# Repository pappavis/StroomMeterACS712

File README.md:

Measure AC power usage using ESP8266 and ACS712

Werk-in-uitvoering!!!

# Waarom?
De bedoeling is om een 230V AC middels software te kunnen aan/uitzetten.  In principe kunt je dit gebruiken waar je AC stroom willen aan/uitzetten en meten. Het functioneert in principe dezelfde als een Sonoff POW switch.

# Hoe werkt het
Wanneer IO-pin HIGH op de ESP32 gaat de voeding aan, aangestuurd door Octoprint, vlak voor starten met printen.

# KiCAD schema

# Benodigheden
De volgende heb je nodig;

|Aantal|Item|Kosten|Optioneel|Data / info|
|------|----|------|---------|--|
|1x|<a href="https://nl.aliexpress.com/item/1005004344359250.html?spm=a2g0o.cart.0.0.6ca561d7aq0PVO&mp=1&gatewayAdapt=glo2nld" alt="MCU verplicht">ESP32 S2 Mini</a> met Bluetooth &amp; WiFi|€2,28|N|<a href="https://www.wemos.cc/en/latest/s2/s2_mini.html">datasheet</a>|
|1x|<a href="https://nl.aliexpress.com/item/32949264545.html?spm=a2g0o.productlist.main.1.1964577aTEmXD6&algo_pvid=6153c03f-b4b4-4653-a854-14e6c40e5aa0&aem_p4p_detail=202301040356468264624950022100000543353&algo_exp_id=6153c03f-b4b4-4653-a854-14e6c40e5aa0-0&pdp_ext_f=%7B%22sku_id%22%3A%2266268030503%22%7D&pdp_npi=2%40dis%21EUR%211.11%211.11%21%21%21%21%21%402145288516728334064801617d0767%2166268030503%21sea&curPageLogUid=MFJIrYuofizE&ad_pvid=202301040356468264624950022100000543353_1&ad_pvid=202301040356468264624950022100000543353_1" alt="AC stroom meten tot 20A">ACS712-05</a> breakout board|€1,11|N|<a href="https://octopart.com/datasheet/acs712elctr-05b-t-allegro+microsystems-38944601">datasheet</a>|J|
|1x|<a href="https://nl.aliexpress.com/item/32808620818.html?spm=a2g0o.order_list.order_list_main.5.2b0a79d2QUDt5m&gatewayAdapt=glo2nld">SRD-03VDC-SL-C 10A 250V</a> relay|€2,44|N|<a href="http://www.datasheetcafe.com/srd-05vdc-sl-c-datasheet-pdf/" alt="verplicht. aan uit schakelaar">datasheet</a>|
|1x|I2C <a href="https://nl.aliexpress.com/item/32672327708.html?spm=a2g0o.cart.0.0.5e6f61d7sThdsn&mp=1&gatewayAdapt=glo2nld" target="_blank">Oled 128X32 scherm</a>|€1,38|J|datasheet|
|1x|<a href="https://nl.aliexpress.com/item/1005003568092031.html?spm=a2g0o.productlist.main.7.30e378e19RwleU&algo_pvid=45aa2b55-53f0-4cf6-be4c-6e9c11d61f6f&aem_p4p_detail=202301040503385945494397516960000675494&algo_exp_id=45aa2b55-53f0-4cf6-be4c-6e9c11d61f6f-3&pdp_ext_f=%7B%22sku_id%22%3A%2212000030654022470%22%7D&pdp_npi=2%40dis%21EUR%215.04%213.93%21%21%21%21%21%402145265416728374183238677d0782%2112000030654022470%21sea&curPageLogUid=Hf4C5MspqKPZ&ad_pvid=202301040503385945494397516960000675494_4&ad_pvid=202301040503385945494397516960000675494_4">SPDT</a> tuimelschakelaar|€0,10|N|<a href="https://www.electronicshub.org/switches/" alt="hulp artikel">info</a>|
|1x|I2C <a href="https://nl.aliexpress.com/item/1005001682363363.html?spm=a2g0o.productlist.main.1.59bf3ddaYob59r&algo_pvid=b5a2e4fa-2b1d-4794-aa8b-f1d2eecffdef&aem_p4p_detail=202301040508292990992845371040000686338&algo_exp_id=b5a2e4fa-2b1d-4794-aa8b-f1d2eecffdef-0&pdp_ext_f=%7B%22sku_id%22%3A%2212000017115738926%22%7D&pdp_npi=2%40dis%21EUR%211.97%211.97%21%21%21%21%21%402145265416728377092613039d0782%2112000017115738926%21sea&curPageLogUid=OZkt1SVUV4Va&ad_pvid=202301040508292990992845371040000686338_1&ad_pvid=202301040508292990992845371040000686338_1">PCF8574P</a> 8-bit expander|€0,20|N|<a href="https://github.com/mcauser/micropython-pcf8574">info</a>|
|2|Screw <a href="https://nl.aliexpress.com/w/wholesale-screw-terminals.html?catId=0&initiative_id=AS_20230210044355&SearchText=screw+terminals&spm=a2g0o.cart.1000002.0" target="_blank">terminals</a>|€0,10|-|-|

Je kunt van Aliexpress bestellen die in één pakketje worden opgestuurd.

# Papier concept versie
TODO: onderstaand schema uitleggen.<br>
<br>
Credits: Max50

# Geïnspireerd door
heb de kunstje beetje geleend van;
 * <a href="https://www.youtube.com/watch?v=dQNBeAZpRmk" target="_blank">Deze</a> videoclip.
 * OctoPrint <a href="https://plugins.octoprint.org/plugins/psucontrol/" target="_blank">psucontrol</a> uitbreiding.

# Algemeen foto's
ACS712 breakout board &amp; <a href="https://octopart.com/datasheet/acs712elctr-05b-t-allegro+microsystems-38944601" target="_blank">datasheet</a>:<br>
</img>
<br>

Tip: PCB gcode voor jouw CNC machine kunt je genereren voor met <a href="http://flatcam.org" target="_blank">Flatcam.org</a>

Credit: <a href="https://www.youtube.com/@easylab4kids246" target="_blank">#easylab4kids</a>

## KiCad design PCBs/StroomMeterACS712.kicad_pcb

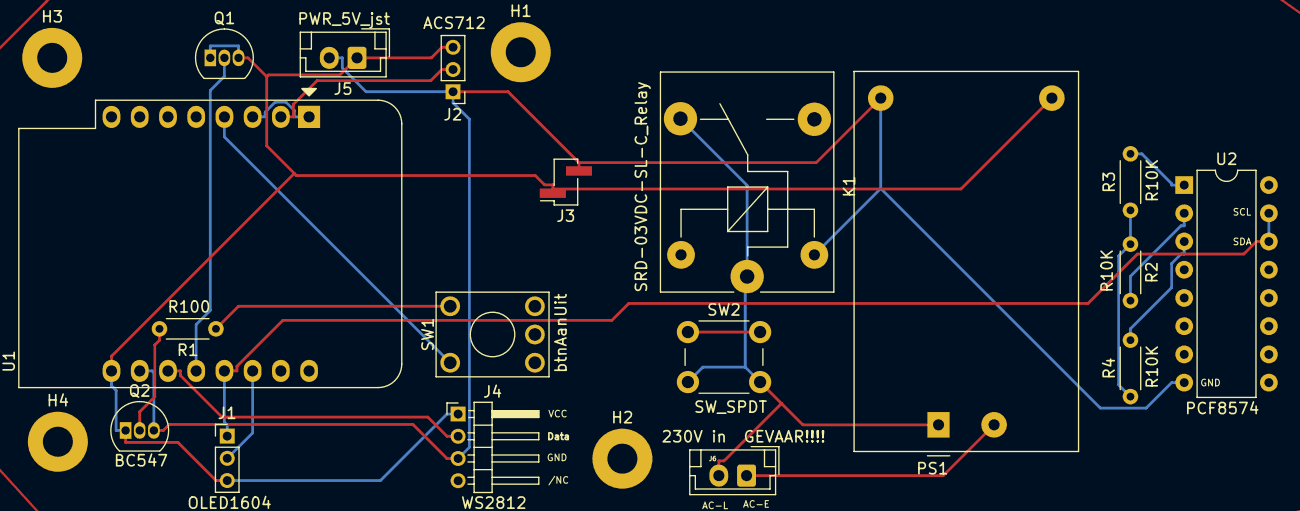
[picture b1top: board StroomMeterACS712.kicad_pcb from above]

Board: 2 copper layers, 22 parts (0 on the bottom side), 17 nets.

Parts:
H1, H2, H3, H4: Gaatje; MountingHole_2.7mm_M2.5_Pad
J1: OLED1604; PinHeader_1x03_P2.00mm_Vertical
J2: ACS712; PinHeader_1x03_P2.00mm_Vertical
J3: PWR_5V_pin; PinHeader_1x02_P2.00mm_Vertical_SMD_Pin1Right
J4: WS2812; PinHeader_1x04_P2.00mm_Horizontal
J5: PWR_5V_jst; JST_EH_B2B-EH-A_1x02_P2.50mm_Vertical
J6: 230V_in; JST_EH_B2B-EH-A_1x02_P2.50mm_Vertical
K1: SRD-03VDC-SL-C_Relay; Relay_SPDT_SANYOU_SRD_Series_Form_C
PS1: HLK-PM01_220V; Converter_ACDC_HiLink_HLK-PMxx
Q1, Q2: BC547; TO-92_Inline
R1: R100; R_Axial_DIN0204_L3.6mm_D1.6mm_P5.08mm_Horizontal
R2, R3, R4: R10K; R_Axial_DIN0204_L3.6mm_D1.6mm_P5.08mm_Horizontal
SW1: btnAanUit; KSA_Tactile_SPST
SW2: SW_SPDT; SW_PUSH_6mm
U1: WeMos_D1_mini; WEMOS_D1_mini_light
U2: PCF8574A; DIP-16_W7.62mm

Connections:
+5V: R2.1, R3.1, R4.1
ACS_AanUit: Q1.2 (B), U1.12 (D3), U2.4 (P0)
ACS_DATA: J2.2, U1.2 (A0)
AC/L: J6.2, K1.1, K1.4, PS1.1 (AC/L), SW2.2 (B)
BTN1: SW1.1, U1.4 (SCK/D5)
DpSlp: U1.1 (~RST), U1.3 (D0)
GND: J2.1, J3.2, J4.3, J5.2, K1.2, PS1.3 (-Vout), Q2.3 (E), U1.10 (GND), U2.8 (VSS)
unnamed: J6.1, PS1.2 (AC/N)
unnamed: Q2.2 (B), R1.2
unnamed: R1.1, SW1.2
unnamed: R3.2, U2.1 (A0)
unnamed: R2.2, U2.2 (A1)
unnamed: R4.2, U2.3 (A2)
SCL: J1.2, U1.14 (SCL/D1), U2.14 (SCL)
SDA: J1.1, U1.13 (SDA/D2), U2.15 (SDA)
VCC: J1.3, J2.3, J3.1, J4.1, J5.1, PS1.4 (+Vout), Q1.1 (C), Q1.3 (E), Q2.1 (C), U1.9 (5V)
WS2812: J4.2, U1.11 (D4)

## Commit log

2022-12-06 werk in uitvoering!!
    gemaakt met http://www.falstad.com/circuit/circuitjs.html
2022-12-08 algemeen1
2022-12-08 labels bijgewerkt
2022-12-09 hernoemd
2022-12-09 bijgewerkt
2022-12-20 WS2812 toegevoegd
2023-01-03 PCb toegeovegd
2023-01-04 PCF8574 toegevoegd
2023-01-04 Nijgewerkt
2023-02-08 PCF8574 toegevoegd aan PCB
2023-02-15 Opgewaardeerd naar KiCAD 7.0
2023-03-23 Omgezet naar KiCAD 7.0
2023-04-01 verplaatsing
2023-06-06 autorouter toegevoegd
